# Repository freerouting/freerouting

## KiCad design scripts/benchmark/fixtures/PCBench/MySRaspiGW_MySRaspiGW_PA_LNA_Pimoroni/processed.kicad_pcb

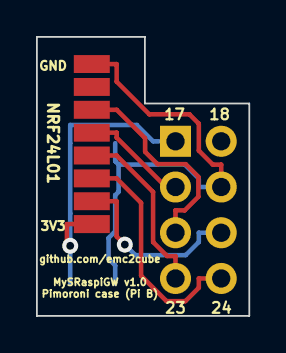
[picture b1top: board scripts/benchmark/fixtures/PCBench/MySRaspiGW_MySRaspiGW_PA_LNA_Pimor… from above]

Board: 2 copper layers, 11.8 x 15.5 mm, 5 parts (0 on the bottom side), 7 nets.

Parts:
C1: 0.1µF; C_0805_HandSoldering
C2: 4.7µF; C_0805_HandSoldering
C3: 47µF; C_0805_HandSoldering
P1: CONN_02X04; Socket_Strip_Straight_2x04
U1: NRF24L01; NRF24L01_PA_LNA-SMD

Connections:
+3V3: C1.1, C2.1, C3.1, P1.1, U1.2
CE: P1.6, U1.3
CSN: P1.8, U1.4
GND: C1.2, C2.2, C3.2, P1.4, U1.1
MISO: P1.5, U1.7
MOSI: P1.3, U1.6
SCK: P1.7, U1.5

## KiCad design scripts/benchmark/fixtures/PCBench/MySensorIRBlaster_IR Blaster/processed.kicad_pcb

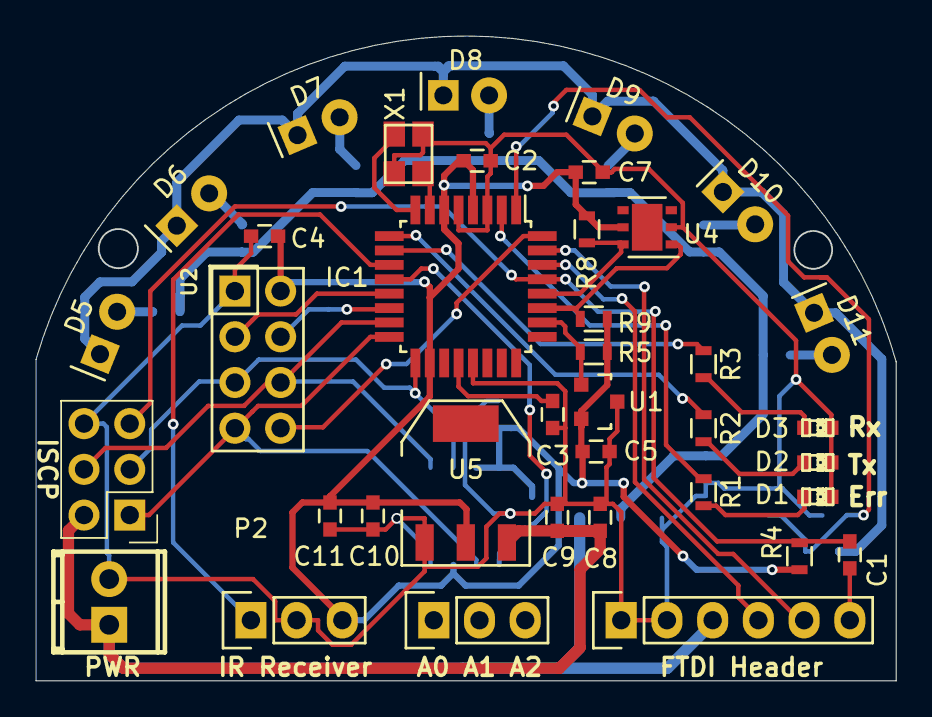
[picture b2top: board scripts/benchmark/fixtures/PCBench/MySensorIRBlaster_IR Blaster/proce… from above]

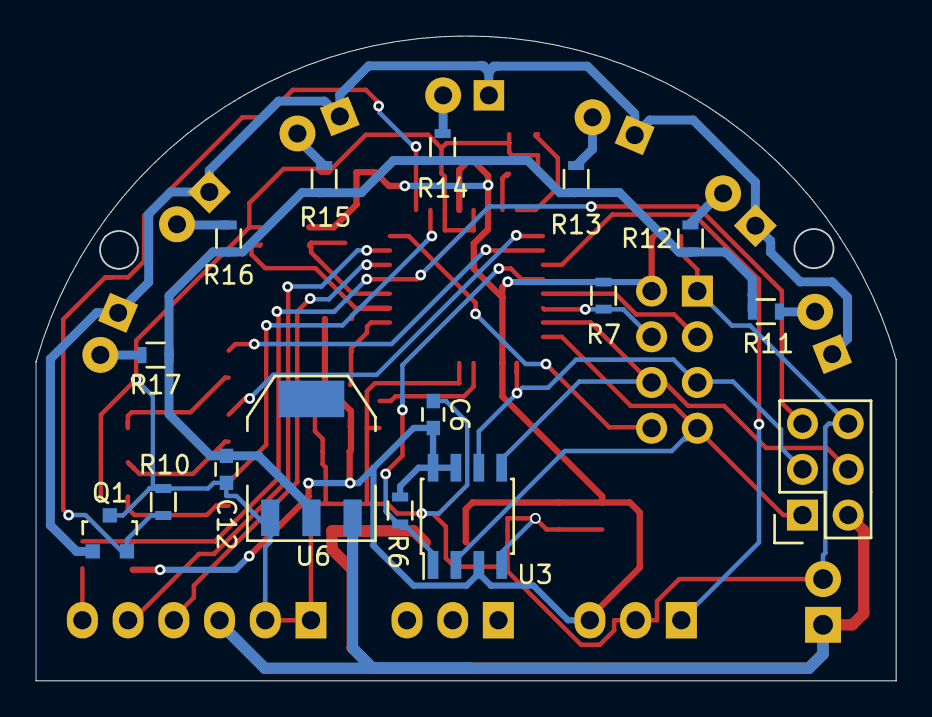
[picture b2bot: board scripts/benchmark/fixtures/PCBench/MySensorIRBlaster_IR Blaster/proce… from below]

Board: 2 copper layers, 47.8 x 35.8 mm, 53 parts (16 on the bottom side), 37 nets.

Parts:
C1, C2, C3, C4, C5, C6, C7, C9, C11: 0.1uF; C_0603
C8, C10: 10uF; C_0603
C12: 22uF; C_0603
CON1: AVR-ISP-6; Socket_Strip_Straight_2x03
D1: Err; LED-0603
D2: Tx; LED-0603
D3: Rx; LED-0603
D5, D6, D7, D8, D9, D10, D11: IR LED; LED-5MM-Horizontal
IC1: ATMEGA328P-A; TQFP-32_7x7mm_Pitch0.8mm
P1: FTDI Header; Pin_Header_Straight_1x06
P2: IR Receiver; Socket_Strip_Straight_1x03
P3: Analog IN; Pin_Header_Straight_1x03
P4: PWR; TerminalBlock2.54mmx2-kcswalter
Q1: FDV303N; SOT-23
R1, R2, R3, R11, R12, R13, R14, R15, R16, R17: R; R_0603
R4: 10K; R_0603
R5, R6, R7, R8, R9, R10: 10k; R_0603
U1: ATSHA204A; SOT-23
U2: NRF24L01
U3: AT25DF512C; SOIC-8_3.9x4.9mm_Pitch1.27mm
U4: Si7021; DFN-6-1EP_3x3mm_Pitch0.95mm
U5: AMS1117-3.3; SOT-223
U6: AMS1117-5.0; SOT-223
X1: CRYSTAL; crystal_FA238-TSX3225

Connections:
+3V3: C2.1, C4.1, C5.1, C6.1, C7.1, C10.1, C11.1, IC1.4, IC1.6, IC1.18, P2.3, R4.1, R5.1, R6.1, R7.2, R8.2, R9.1, U1.2, U2.2, U3.3, U3.7, U3.8, U4.5, U5.2
+5V: C12.1, R11.1, R12.1, R13.1, R14.1, R15.1, R16.1, R17.1, U6.2
/A3: IC1.26, R5.2, U1.1
/D2: IC1.32, U2.8
/D3: IC1.1, Q1.2, R10.2
/D4: IC1.2, R1.2
/D5: IC1.9, R2.2
/D6: IC1.10, R3.2
/D7: IC1.11, P2.1
/D8: IC1.12, R6.2, U3.1
/D9: IC1.13, U2.3
/D10: IC1.14, R7.1, U2.4
/DTR: C1.1, P1.6
/MISO: CON1.1, IC1.16, U2.7, U3.2
/MOSI: CON1.4, IC1.15, U2.6, U3.5
/RESET: C1.2, CON1.5, IC1.29, R4.2
/RXD: IC1.30, P1.4
/SCK: CON1.3, IC1.17, U2.5, U3.6
/SCL: IC1.28, R8.1, U4.6
/SDA: IC1.27, R9.2, U4.1
/TXD: IC1.31, P1.5
/XTAL1: IC1.7, X1.1
/XTAL2: IC1.8, X1.2
GND: C2.2, C3.2, C4.2, C5.2, C6.2, C7.2, C8.2, C9.2, C10.2, C11.2, C12.2, CON1.6, D1.1, D2.1, D3.1, IC1.3, IC1.5, IC1.21, P1.1, P1.2, P2.2, P4.2, Q1.3, R10.1, U1.3, U2.1, U3.4, U4.2, U5.1, U6.1, X1.3
unnamed: C3.1, IC1.20
unnamed: D1.2, R1.1
unnamed: D2.2, R2.1
unnamed: D3.2, R3.1
unnamed: D5.2, R11.2
unnamed: D6.2, R12.2
unnamed: D7.2, R13.2
unnamed: D8.2, R14.2
unnamed: D9.2, R15.2
unnamed: D5.1, D6.1, D7.1, D8.1, D9.1, D10.1, D11.1, Q1.1
unnamed: D10.2, R16.2
unnamed: D11.2, R17.2
VCC: C8.1, C9.1, CON1.2, P1.3, P4.1, U5.3, U6.3
